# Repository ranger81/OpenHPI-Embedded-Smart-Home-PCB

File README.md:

# OpenHPI Embedded Smart Home PCB

Fertiges Platinenlayout für das OpenHPI Embedded Smart Home Project 06/2016.

Ich habe mir das nötige Platinenlayout in Eagle nochmal nachgezeichnet (inkl. der zwei fehlenden Pulldown-Widerstände) und mir selbst eine einseitige Platine hergestellt. Vielleicht kann ja jemand mein Layout brauchen...

Die Selberätzer können sich das Layout im Repository oder hier als PDF herunterladen: https://www.ranger81.de/_sub/temp/EmbeddedSmartHomePCB.pdf Das Layout ist für die Unterseite der Platine, entsprechend nicht gespiegelt ausdrucken.

Im Repository oder hier ein Foto der fertig bestückten Platine: https://www.ranger81.de/_sub/temp/EmbeddedSmartHomePCBFoto.jpg

Hier ein Video mit Anleitung zum Platinen herstellen: https://youtu.be/-L1i9SnYGaU

Anstatt dem Feuchtigkeit und Temperatursensor verwende ich einfache Thermistoren. Die Sensoren gibt es bei Conrad derzeit nicht mehr lieferbar, deswegen ist der Schaltplan an dieser Stelle auch etwas modifiziert, um einfach irgendwelche "dummy"-Werte zu liefern. Wer den richtigen Sensor hat, muss den Schaltplan also noch ein klein wenig umbauen mit Hilfe der Daten auf GitHub und der Freeware-Version von Eagle.

Grüße Tobi

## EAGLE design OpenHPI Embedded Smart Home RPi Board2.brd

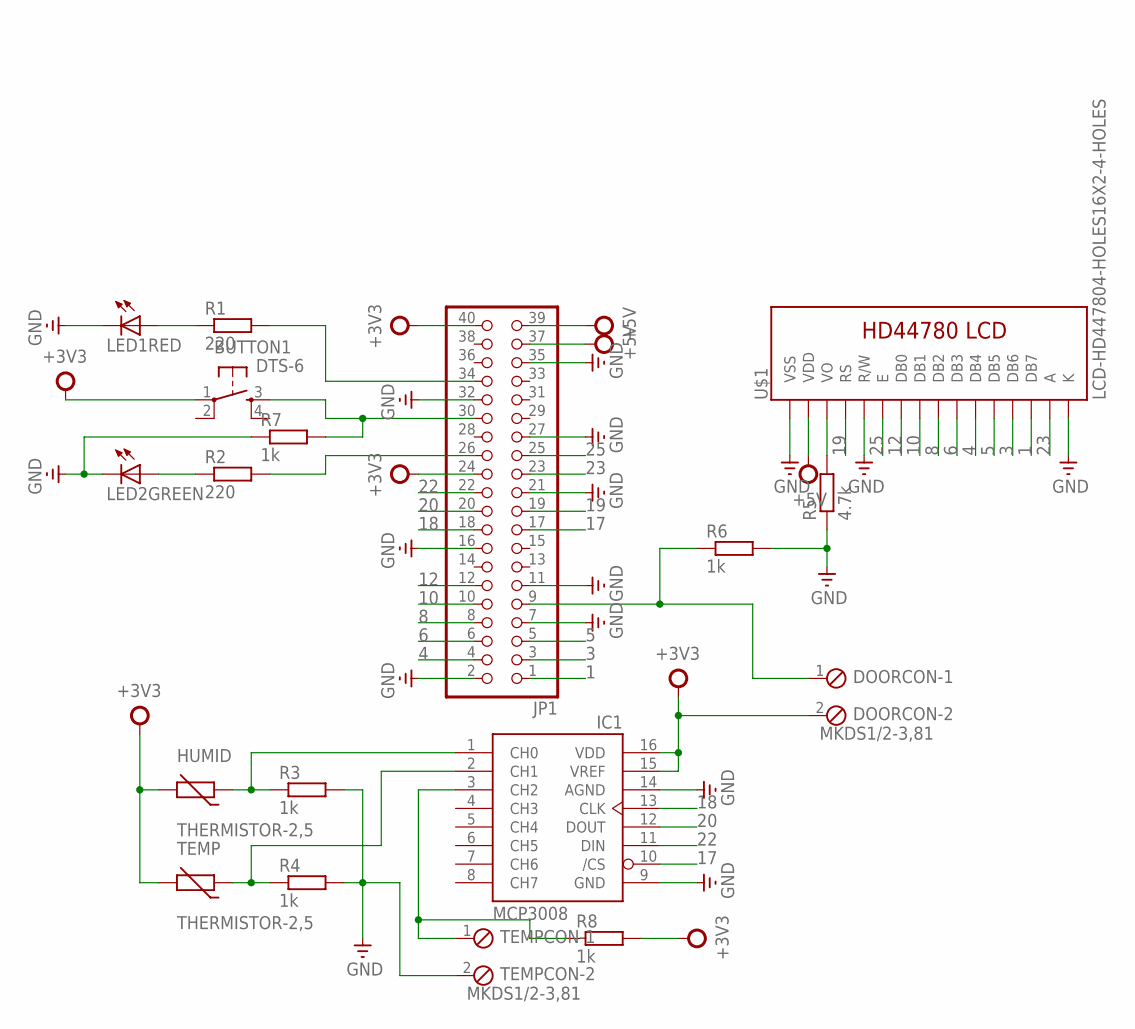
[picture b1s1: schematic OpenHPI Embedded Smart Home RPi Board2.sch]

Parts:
BUTTON1: DTS-6
DOORCON: MKDS1/2-3,81; 2POL381
HUMID: THERMISTOR-2,5; RS-2,5
IC1: MCP3008; DIL16
JP1: PINHD-2X20; 2X20
LED1RED, LED2GREEN: LED5MM
R1, R2: 220; 0207/7
R3, R4, R6, R7, R8: 1k; 0207/7
R5: 4.7k; 0207/7
TEMP: THERMISTOR-2,5; RS-2,5
TEMPCON: MKDS1/2-3,81; 2POL381
U$1: LCD-HD447804-HOLES16X2-4-HOLES; LCD-16X2-4HOLES

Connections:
1: JP1.1, U$1.14 (DB7)
3: JP1.3, U$1.13 (DB6)
4: JP1.4, U$1.11 (DB4)
5: JP1.5, U$1.12 (DB5)
6: JP1.6, U$1.10 (DB3)
8: JP1.8, U$1.9 (DB2)
10: JP1.10, U$1.8 (DB1)
12: JP1.12, U$1.7 (DB0)
17: IC1.10 (/CS), JP1.17
18: IC1.13 (CLK), JP1.18
19: JP1.19, U$1.4 (RS)
20: IC1.12 (DOUT), JP1.20
22: IC1.11 (DIN), JP1.22
23: JP1.23, U$1.15 (A)
25: JP1.25, U$1.6 (E)
+3V3: BUTTON1.1, DOORCON.2, HUMID.2, IC1.15 (VREF), IC1.16 (VDD), JP1.24, JP1.40, R8.2, TEMP.2
+5V: JP1.37, JP1.39, U$1.2 (VDD)
GND: IC1.9 (GND), IC1.14 (AGND), JP1.2, JP1.7, JP1.11, JP1.16, JP1.21, JP1.27, JP1.32, JP1.35, LED1RED.K (C), LED2GREEN.K (C), R3.2, R4.2, R5.1, R6.2, R7.1, TEMPCON.2, U$1.1 (VSS), U$1.5 (R/W), U$1.16 (K)
unnamed: LED1RED.A, R1.1
unnamed: LED2GREEN.A, R2.1
unnamed: R5.2, U$1.3 (VO)
unnamed: BUTTON1.3, JP1.30, R7.2
unnamed: JP1.34, R1.2
unnamed: JP1.26, R2.2
unnamed: HUMID.1, IC1.1 (CH0), R3.1
unnamed: IC1.2 (CH1), R4.1, TEMP.1
unnamed: IC1.3 (CH2), R8.1, TEMPCON.1
unnamed: DOORCON.1, JP1.9, R6.1

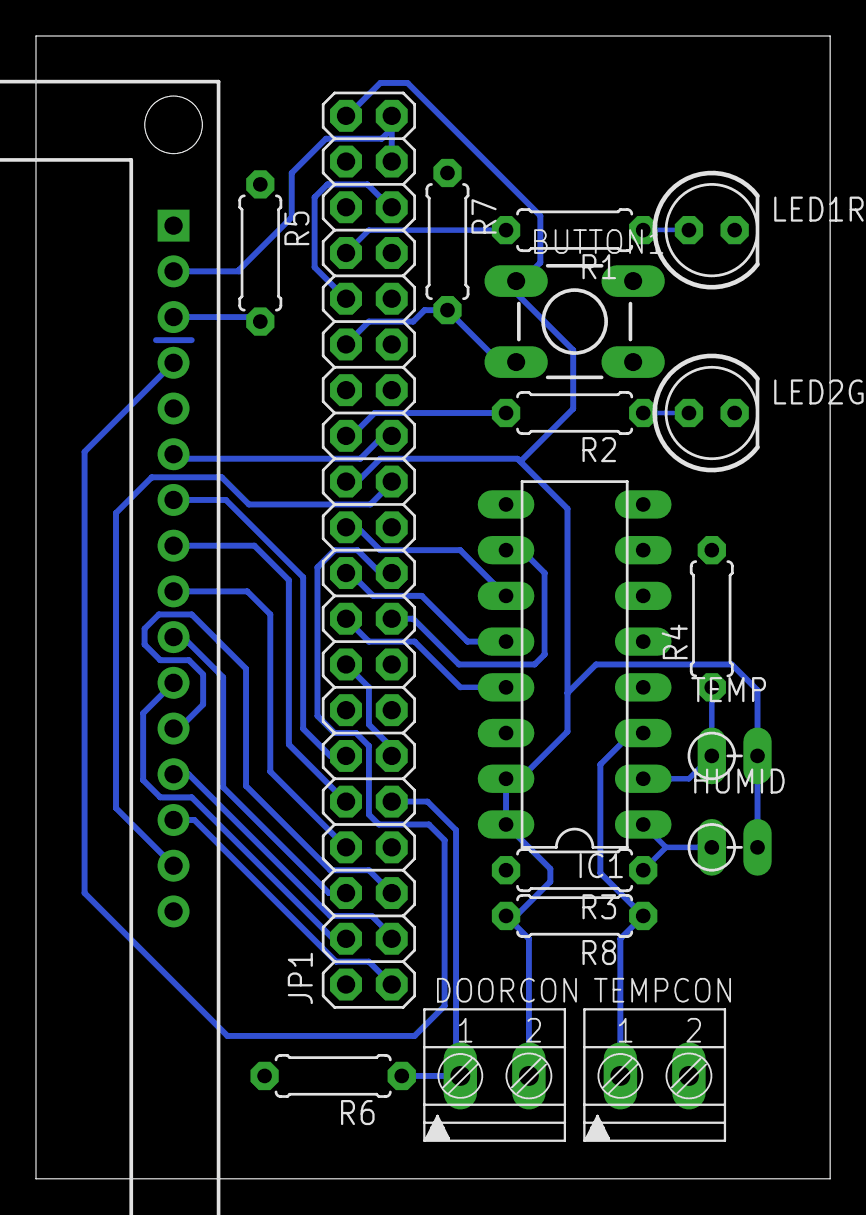
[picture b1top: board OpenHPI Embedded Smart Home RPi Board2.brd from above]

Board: 2 copper layers, 44.1 x 63.5 mm, 18 parts (0 on the bottom side), 28 nets.

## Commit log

2016-06-04 Correcture
